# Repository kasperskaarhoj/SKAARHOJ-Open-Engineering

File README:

SKAARHOJ Open Engineering repository contains most of the freely available information on our hardware designs. You can find much more information about this project at http://skaarhoj.com/ and specifically the wiki pages at http://skaarhoj.com/wiki/

License:
All software is GNU-GPL and everything else is Creative Commons BY-SA unless otherwise noted. Please check out this page for information on how to use our free resources:

http://skaarhoj.com/about/licenses/

The SKAARHOJ Development Team

Kasper Skårhøj

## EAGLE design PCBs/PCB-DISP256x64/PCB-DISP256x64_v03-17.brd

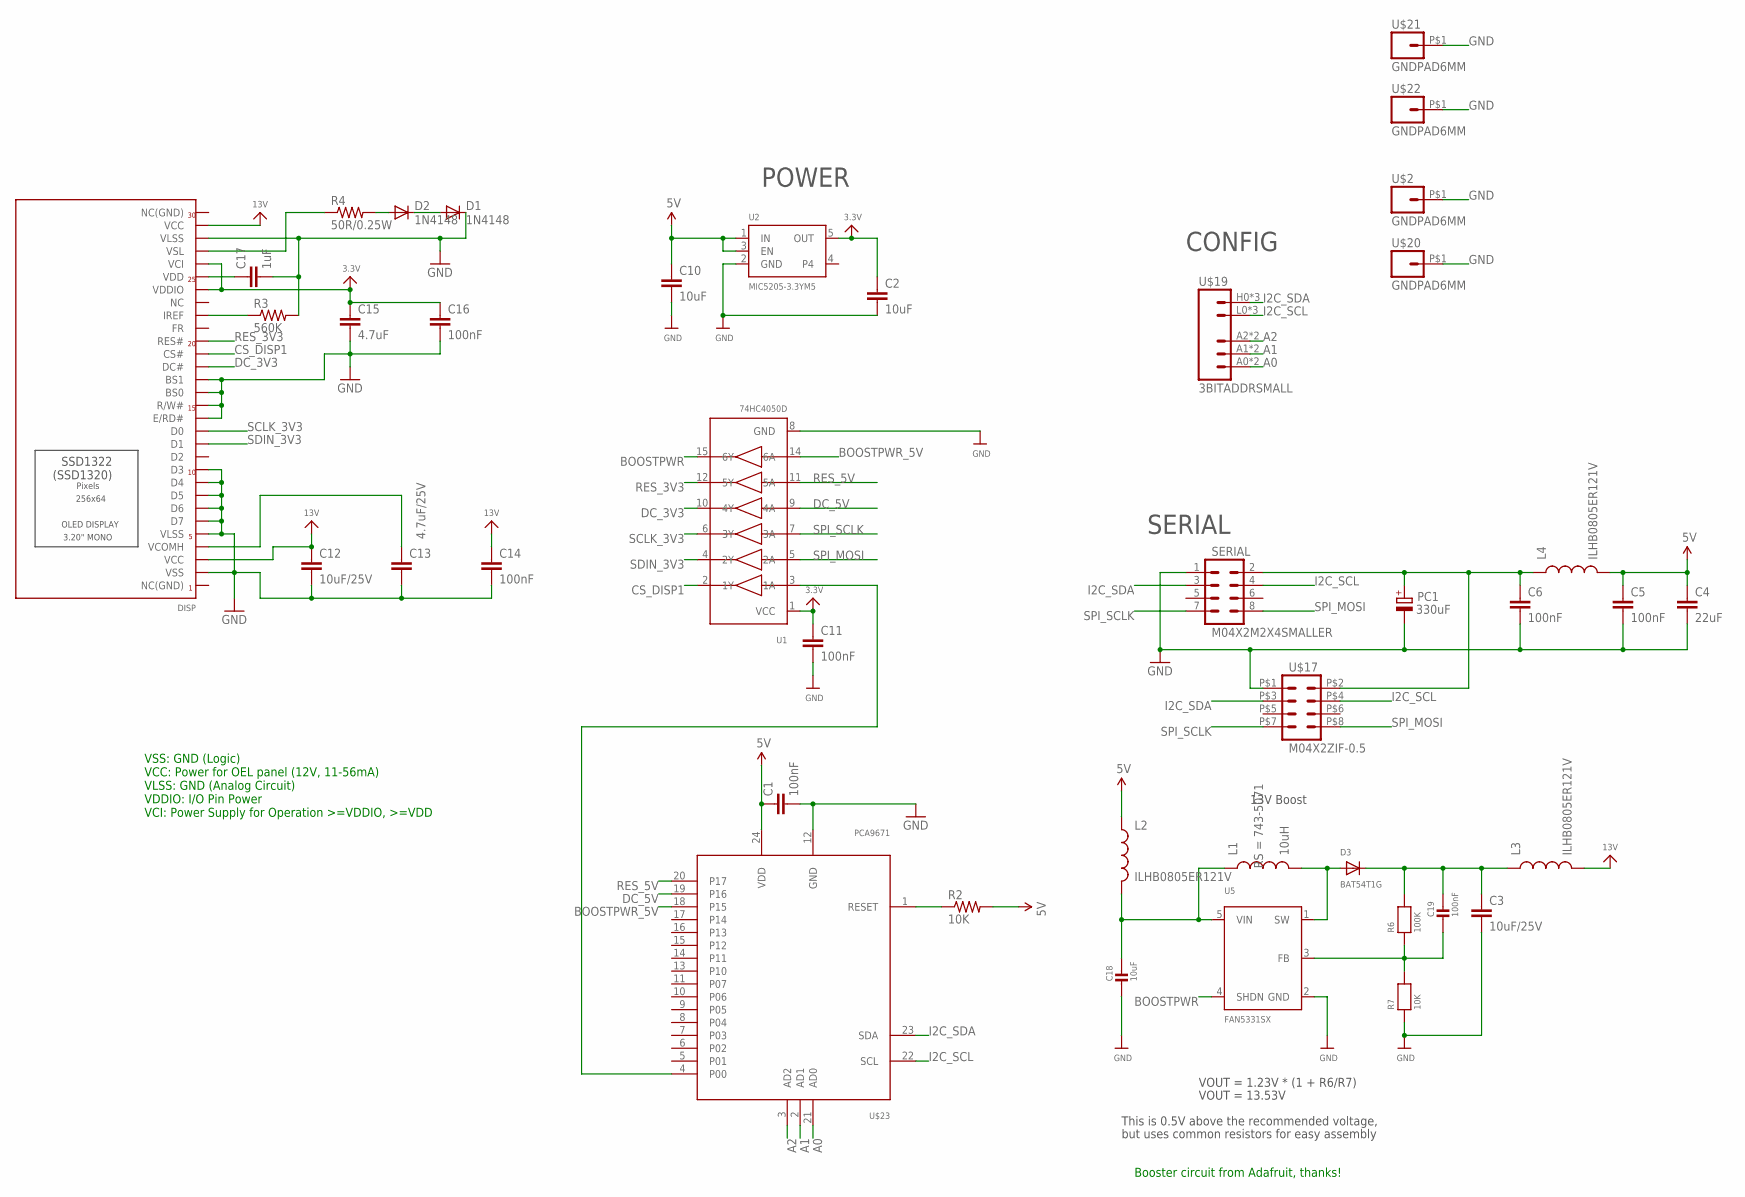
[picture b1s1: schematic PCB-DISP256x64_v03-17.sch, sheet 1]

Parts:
C1, C5, C6, C11, C14, C16: 100nF; 0603-CAP
C2, C10, C18: 10uF; 0805
C3, C12: 10uF/25V; 0805
C4: 22uF; 0805
C13: 4.7uF/25V; 0805
C15: 4.7uF; 0805
C17: 1uF; 0603-CAP
C19: 100nF; 0603
D1, D2: 1N4148; SOD-323
D3: BAT54T1G; SOD-123
DISP: ER_OLED032-1TOP; FPC_XF2M-3015-1A
L1: 10uH; 3015
L2, L3, L4: ILHB0805ER121V; 0805
PC1: 330uF; PANASONIC_D
R2: 10K; 0603-RES
R3: 560K; 0603-RES
R4: 50R/0.25W; 0603-RES
R6: 100K; 0603
R7: 10K; 0603
SERIAL: M04X2M2X4SMALLER; M2X4SMALLER
U1: 74HC4050D; TSSOP16
U2: MIC5205-3.3YM5; SOT23-5
U5: FAN5331SX; SOT23-5@1
U$2, U$20, U$21, U$22: GNDPAD6MM; 3.2MMPAD6MM
U$17: M04X2ZIF-0.5; ZIP-8-0.5
U$19: 3BITADDRSMALL; 3BITADDR_SMALL
U$23: PCA9671; TSSOP24

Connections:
3.3V: C2.1, C11.1, C15.1, C16.1, DISP.P$5 (VCI), DISP.P$7 (VDDIO), U1.1 (VCC), U2.5 (OUT)
5V: C1.1, C4.1, C5.1, C10.1, L2.1, L4.2, R2.2, U2.1 (IN), U2.3 (EN), U$23.24 (VDD)
13V: C12.1, C14.1, DISP.P$2 (VCC), DISP.P$28 (VCC), L3.2
A0: U$19.A0, U$19.AS0 (A0), U$23.21 (AD0)
A1: U$19.A1, U$19.AS1 (A1), U$23.2 (AD1)
A2: U$19.A2, U$19.AS2 (A2), U$23.3 (AD2)
ARD_5V: C6.1, L4.1, PC1.+, SERIAL.2, U$17.P$2 (2)
BOOSTPWR: U1.15 (6Y), U5.4 (SHDN)
BOOSTPWR_5V: U1.14 (6A), U$23.18 (P15)
CS_DISP1: DISP.P$12 (CS#), U1.2 (1Y)
DC_3V3: DISP.P$13 (DC#), U1.10 (4Y)
DC_5V: U1.9 (4A), U$23.19 (P16)
GND: C1.2, C2.2, C3.2, C4.2, C5.2, C6.2, C10.2, C11.2, C12.2, C13.2, C14.2, C15.2, C16.2, C17.2, C18.2, D1.1 (C), DISP.P$3 (VLSS), DISP.P$14 (BS1), DISP.P$15 (BS0), DISP.P$16 (R/W#), DISP.P$17 (E/RD#), DISP.P$21 (D3), DISP.P$22 (D4), DISP.P$23 (D5), DISP.P$24 (D6), DISP.P$25 (D7), DISP.P$26 (VLSS), DISP.P$29 (VSS), PC1.-, R3.2, R7.1, SERIAL.1, U1.8 (GND), U2.2 (GND), U5.2 (GND), U$2.P$1, U$17.P$1 (1), U$20.P$1, U$21.P$1, U$22.P$1, U$23.12 (GND)
I2C_SCL: SERIAL.4, U$17.P$4 (4), U$19.L0 (GND), U$19.L1 (GND), U$19.L2 (GND), U$23.22 (SCL)
I2C_SDA: SERIAL.3, U$17.P$3 (3), U$19.H0 (VCC), U$19.H1 (VCC), U$19.H2 (VCC), U$23.23 (SDA)
unnamed: R2.1, U$23.1 (RESET)
unnamed: C18.1, L1.1, L2.2, U5.5 (VIN)
unnamed: U1.3 (1A), U$23.4 (P00)
unnamed: C3.1, C19.1, D3.C, L3.1, R6.2
unnamed: C13.1, DISP.P$27 (VCOMH)
unnamed: DISP.P$4 (VSL), R4.1
unnamed: DISP.P$9 (IREF), R3.1
unnamed: D2.2 (A), R4.2
unnamed: C17.1, DISP.P$6 (VDD)
unnamed: D1.2 (A), D2.1 (C)
unnamed: D3.A, L1.2, U5.1 (SW)
unnamed: C19.2, R6.1, R7.2, U5.3 (FB)
RES_3V3: DISP.P$11 (RES#), U1.12 (5Y)
RES_5V: U1.11 (5A), U$23.20 (P17)
SCLK_3V3: DISP.P$18 (D0), U1.6 (3Y)
SDIN_3V3: DISP.P$19 (D1), U1.4 (2Y)
SPI_MOSI: SERIAL.8, U1.5 (2A), U$17.P$8 (8)
SPI_SCLK: SERIAL.7, U1.7 (3A), U$17.P$7 (7)

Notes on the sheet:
SERIAL
POWER
CONFIG
VOUT = 1.23V * (1 + R6/R7)
VOUT = 13.53V
This is 0.5V above the recommended voltage,
but uses common resistors for easy assembly
13V Boost
Booster circuit from Adafruit, thanks!
VSS: GND (Logic) VCC: Power for OEL panel (12V, 11-56mA) VLSS: GND (Analog Circuit) VDDIO: I/O Pin Power VCI: Power Supply for Operation >=VDDIO, >=VDD

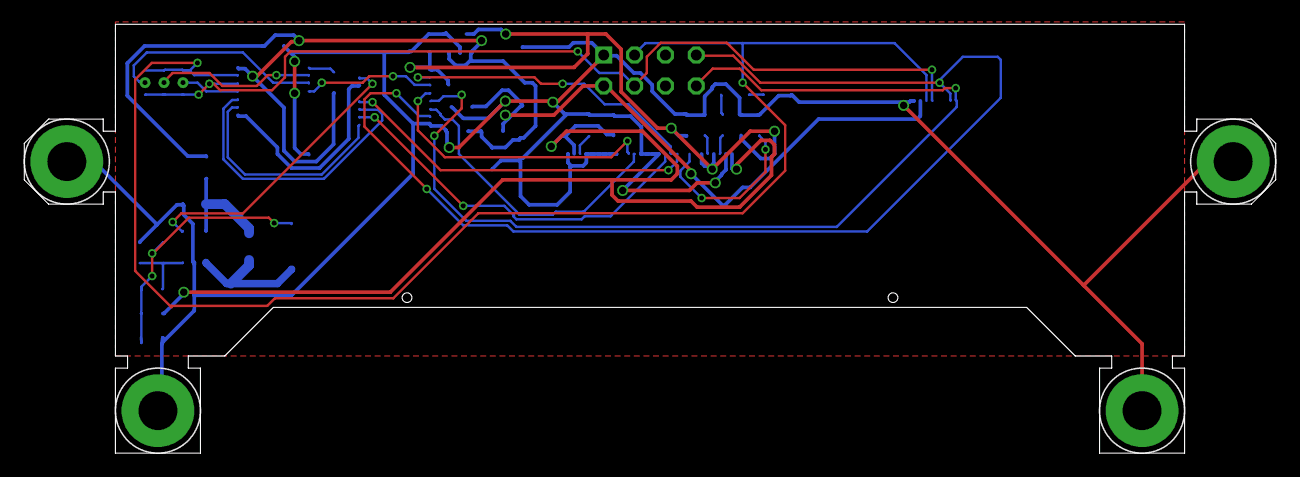
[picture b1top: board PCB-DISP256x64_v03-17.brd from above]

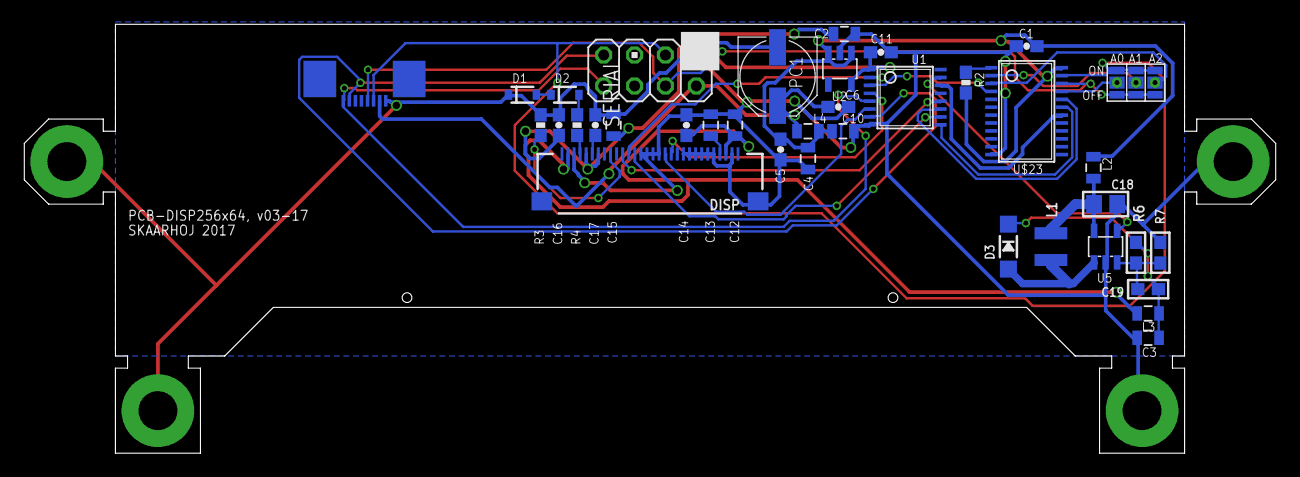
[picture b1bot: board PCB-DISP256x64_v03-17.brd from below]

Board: 2 copper layers, 103.0 x 35.3 mm, 41 parts (37 on the bottom side), 33 nets.

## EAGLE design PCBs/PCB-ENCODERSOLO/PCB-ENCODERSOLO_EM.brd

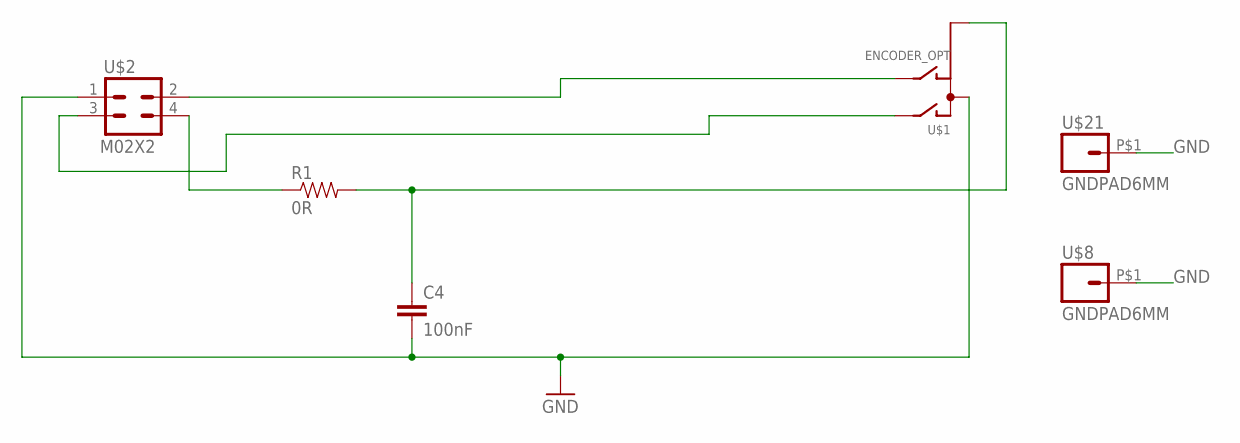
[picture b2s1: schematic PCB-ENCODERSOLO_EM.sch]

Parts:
C4: 100nF; 0603-CAP
R1: 0R; 0603-RES
U$1: ENCODER_OPT; ENCODER_EM14
U$2: M02X2; 2X2
U$8, U$21: GNDPAD6MM; 3.2MMPAD6MM

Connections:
5V: C4.1, R1.2, U$1.2 (5V)
D3: U$1.5 (A), U$2.3
GND: C4.2, U$1.6 (GND), U$1.GND, U$1.GND1 (GND), U$2.1, U$8.P$1, U$21.P$1
unnamed: R1.1, U$2.4
unnamed: U$1.1 (B), U$2.2

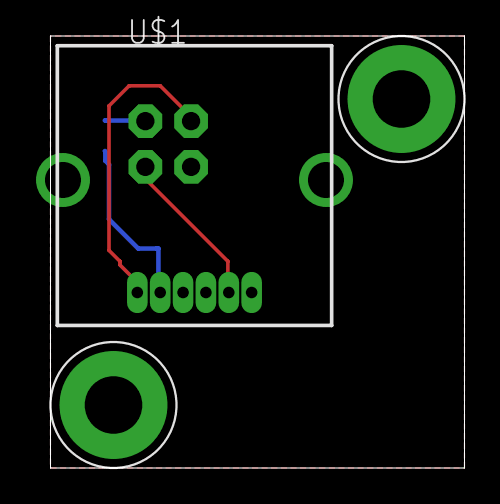
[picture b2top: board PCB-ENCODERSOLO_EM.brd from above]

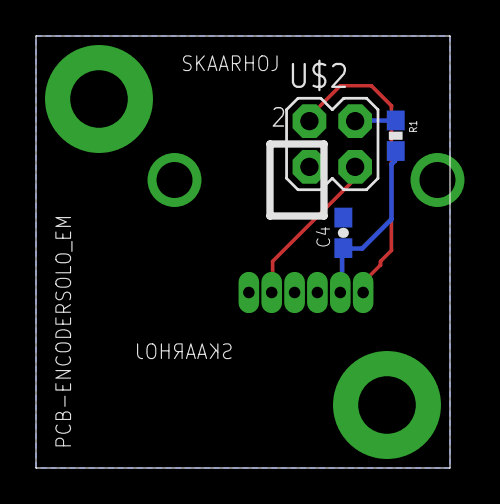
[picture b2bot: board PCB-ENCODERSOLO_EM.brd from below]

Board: 2 copper layers, 23.0 x 24.0 mm, 6 parts (3 on the bottom side), 5 nets.

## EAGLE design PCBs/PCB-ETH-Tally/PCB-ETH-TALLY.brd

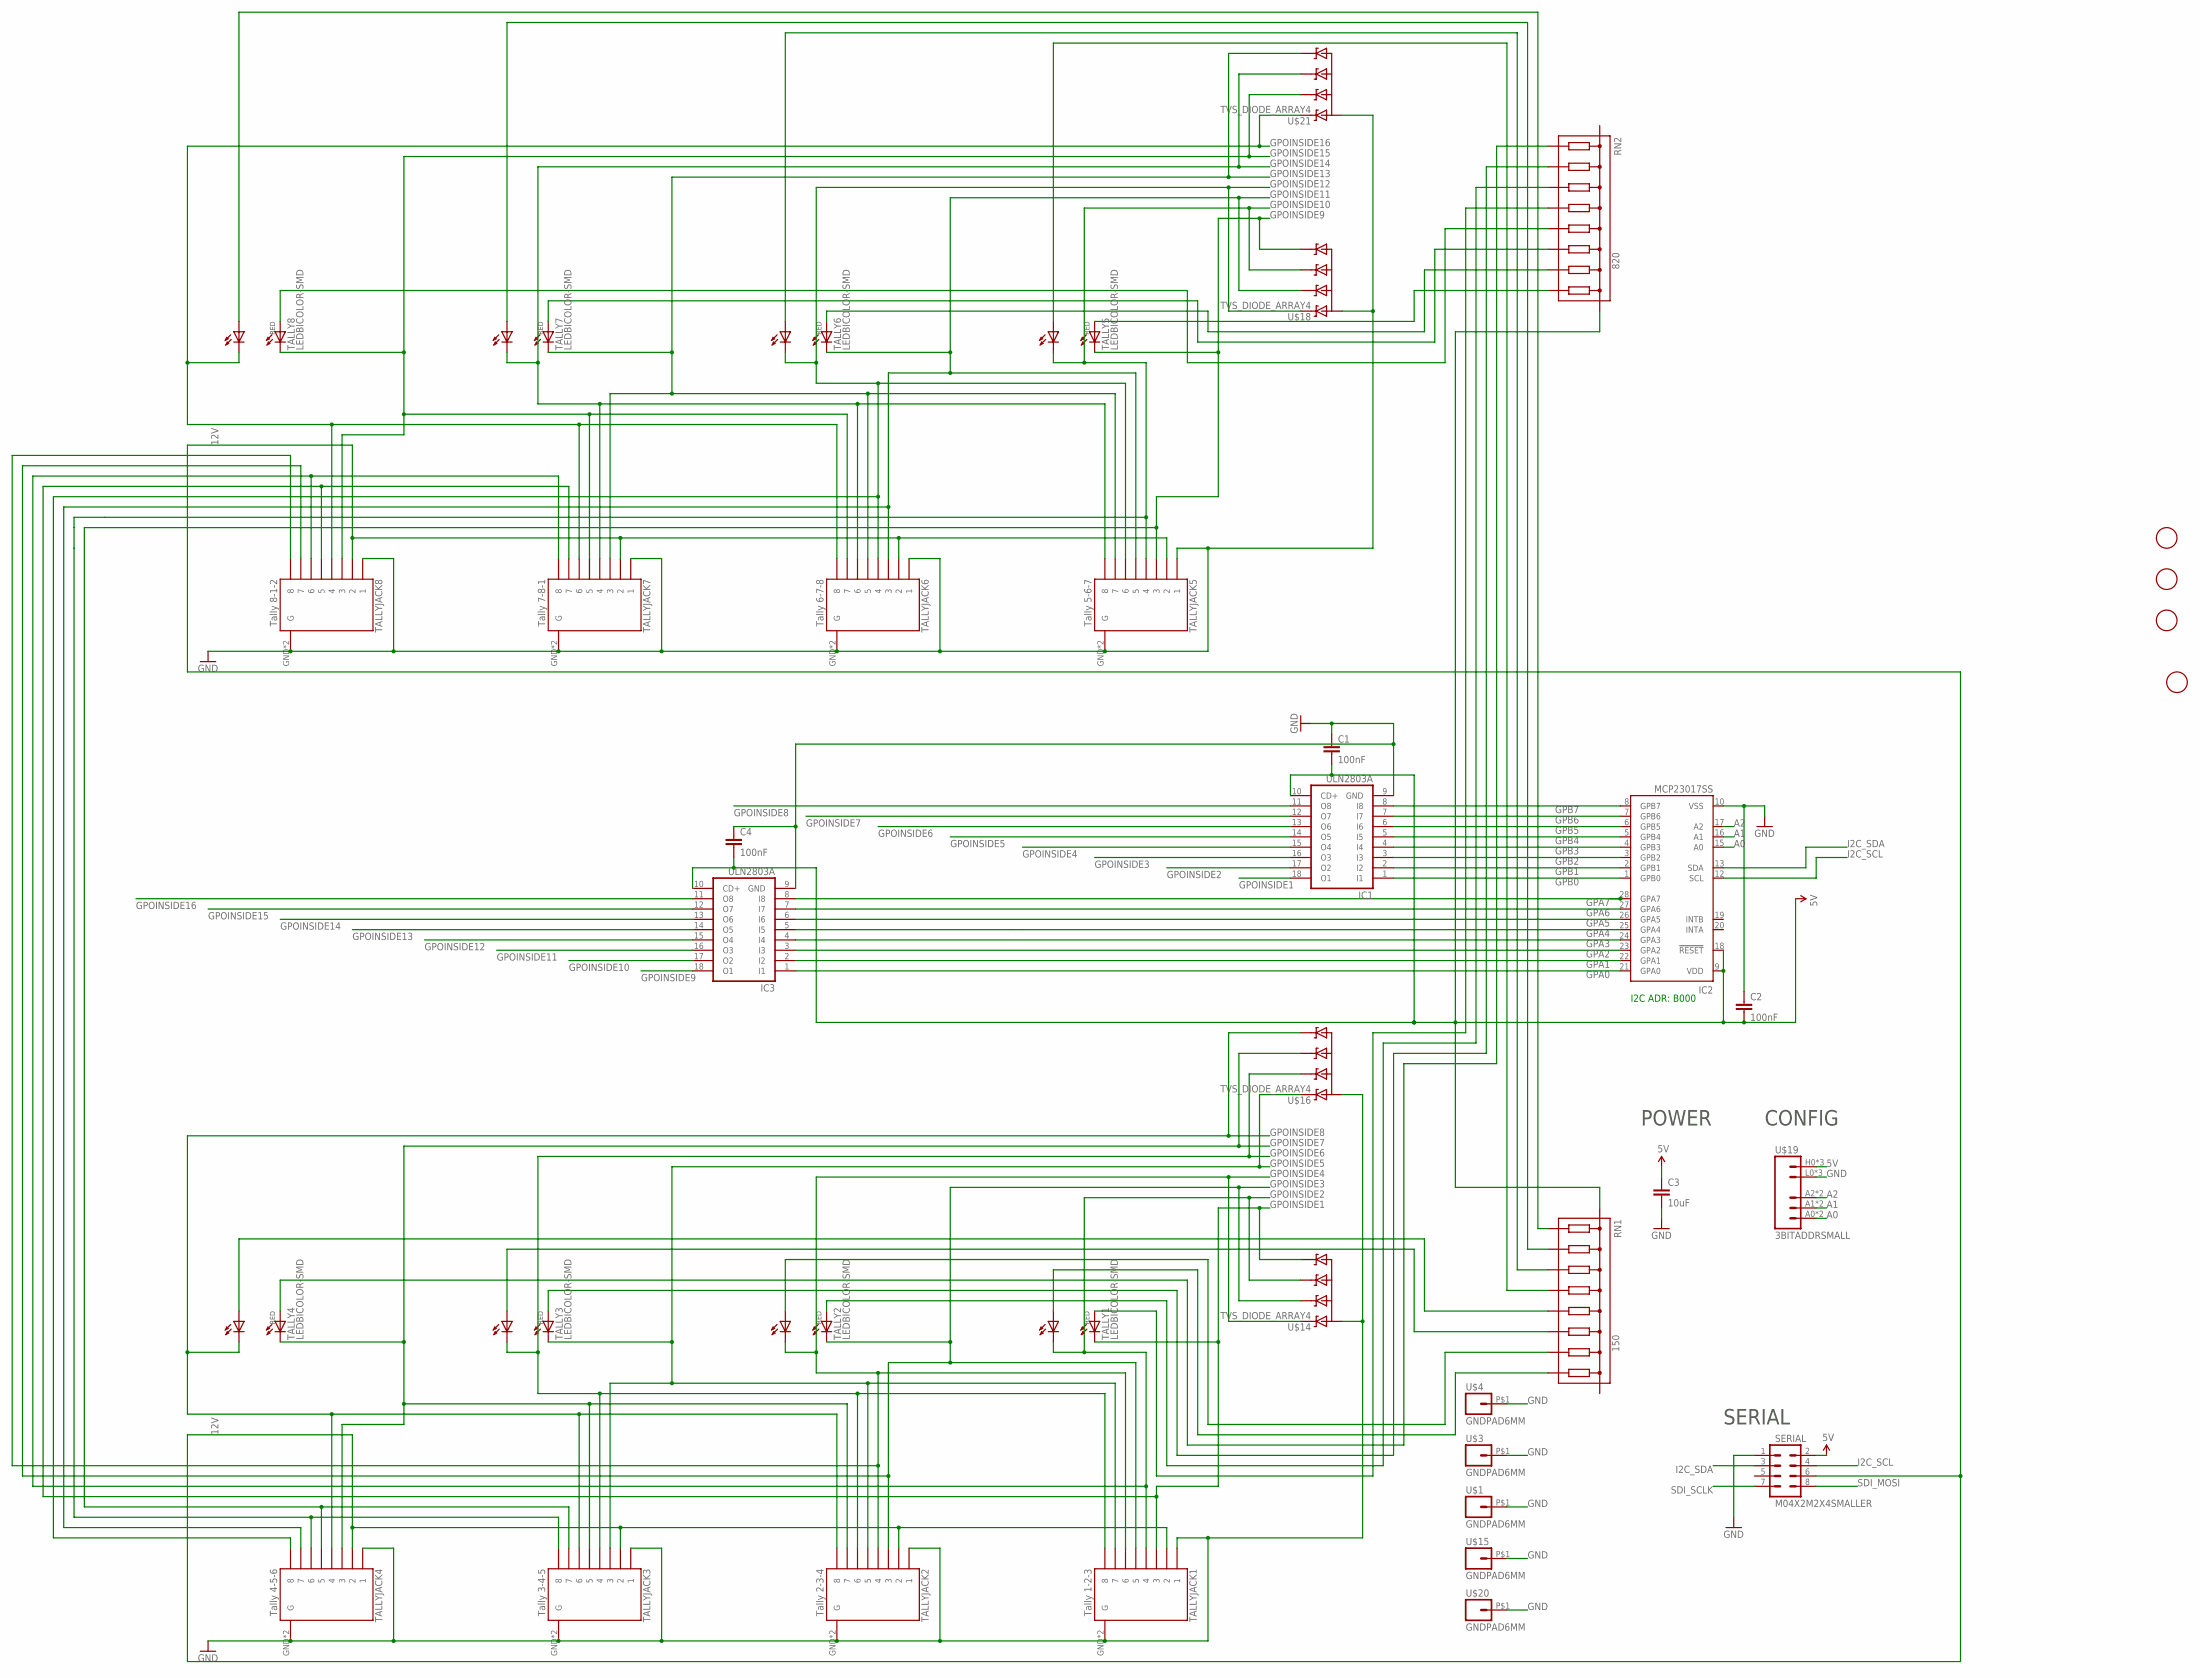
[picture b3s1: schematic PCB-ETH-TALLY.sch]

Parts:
C1, C4: 100nF; 0805
C2: 100nF; 0603-CAP
C3: 10uF; 0805
IC1, IC3: ULN2803A; SO18W
IC2: MCP23017SS; SSOP28
RN1: 150; EXBE
RN2: 820; EXBE
SERIAL: M04X2M2X4SMALLER; M2X4SMALLER
TALLY1, TALLY2, TALLY3, TALLY4, TALLY5, TALLY6, TALLY7, TALLY8: LEDBICOLOR-SMD
TALLYJACK1: Tally 1-2-3; RJ45-8_GND_UPRIGHT
TALLYJACK2: Tally 2-3-4; RJ45-8_GND_UPRIGHT
TALLYJACK3: Tally 3-4-5; RJ45-8_GND_UPRIGHT
TALLYJACK4: Tally 4-5-6; RJ45-8_GND_UPRIGHT
TALLYJACK5: Tally 5-6-7; RJ45-8_GND_UPRIGHT
TALLYJACK6: Tally 6-7-8; RJ45-8_GND_UPRIGHT
TALLYJACK7: Tally 7-8-1; RJ45-8_GND_UPRIGHT
TALLYJACK8: Tally 8-1-2; RJ45-8_GND_UPRIGHT
U$1, U$3, U$4, U$15, U$20: GNDPAD6MM; 3.2MMPAD6MM
U$5, U$6, U$8, U$9: FIDUCIAL; FIDUCIAL_1MM
U$14, U$16, U$18, U$21: TVS_DIODE_ARRAY4; SOT23-6L
U$19: 3BITADDRSMALL; 3BITADDR_SMALL

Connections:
5V: C1.2, C2.2, C3.1, C4.2, IC1.10 (CD+), IC2.9 (VDD), IC2.18 (!RESET), IC3.10 (CD+), RN1.1 (POL), RN2.6 (POL), SERIAL.2, U$19.H0 (VCC), U$19.H1 (VCC), U$19.H2 (VCC)
12V: SERIAL.6, TALLYJACK1.2, TALLYJACK2.2, TALLYJACK3.2, TALLYJACK4.2, TALLYJACK5.2, TALLYJACK6.2, TALLYJACK7.2, TALLYJACK8.2
A0: IC2.15 (A0), U$19.A0, U$19.AS0 (A0)
A1: IC2.16 (A1), U$19.A1, U$19.AS1 (A1)
A2: IC2.17 (A2), U$19.A2, U$19.AS2 (A2)
GND: C1.1, C2.1, C3.2, C4.1, IC1.9 (GND), IC2.10 (VSS), IC3.9 (GND), SERIAL.1, TALLYJACK1.1, TALLYJACK1.GND (G), TALLYJACK1.GND1 (G), TALLYJACK2.1, TALLYJACK2.GND (G), TALLYJACK2.GND1 (G), TALLYJACK3.1, TALLYJACK3.GND (G), TALLYJACK3.GND1 (G), TALLYJACK4.1, TALLYJACK4.GND (G), TALLYJACK4.GND1 (G), TALLYJACK5.1, TALLYJACK5.GND (G), TALLYJACK5.GND1 (G), TALLYJACK6.1, TALLYJACK6.GND (G), TALLYJACK6.GND1 (G), TALLYJACK7.1, TALLYJACK7.GND (G), TALLYJACK7.GND1 (G), TALLYJACK8.1, TALLYJACK8.GND (G), TALLYJACK8.GND1 (G), U$1.P$1, U$3.P$1, U$4.P$1, U$14.2 (GND), U$14.5 (GND), U$15.P$1, U$16.2 (GND), U$16.5 (GND), U$18.2 (GND), U$18.5 (GND), U$19.L0 (GND), U$19.L1 (GND), U$19.L2 (GND), U$20.P$1, U$21.2 (GND), U$21.5 (GND)
GPA0: IC2.21 (GPA0), IC3.1 (I1)
GPA1: IC2.22 (GPA1), IC3.2 (I2)
GPA2: IC2.23 (GPA2), IC3.3 (I3)
GPA3: IC2.24 (GPA3), IC3.4 (I4)
GPA4: IC2.25 (GPA4), IC3.5 (I5)
GPA5: IC2.26 (GPA5), IC3.6 (I6)
GPA6: IC2.27 (GPA6), IC3.7 (I7)
GPA7: IC2.28 (GPA7), IC3.8 (I8)
GPB0: IC1.1 (I1), IC2.1 (GPB0)
GPB1: IC1.2 (I2), IC2.2 (GPB1)
GPB2: IC1.3 (I3), IC2.3 (GPB2)
GPB3: IC1.4 (I4), IC2.4 (GPB3)
GPB4: IC1.5 (I5), IC2.5 (GPB4)
GPB5: IC1.6 (I6), IC2.6 (GPB5)
GPB6: IC1.7 (I7), IC2.7 (GPB6)
GPB7: IC1.8 (I8), IC2.8 (GPB7)
GPOINSIDE1: IC1.18 (O1), TALLY1.P$2 (C), TALLYJACK1.3, TALLYJACK7.7, TALLYJACK8.5, U$14.6 (D)
GPOINSIDE2: IC1.17 (O2), TALLY1.P$4 (C1), TALLYJACK1.4, TALLYJACK7.8, TALLYJACK8.6, U$14.4 (C)
GPOINSIDE3: IC1.16 (O3), TALLY2.P$2 (C), TALLYJACK1.5, TALLYJACK2.3, TALLYJACK8.7, U$14.3 (B)
GPOINSIDE4: IC1.15 (O4), TALLY2.P$4 (C1), TALLYJACK1.6, TALLYJACK2.4, TALLYJACK8.8, U$14.1 (A)
GPOINSIDE5: IC1.14 (O5), TALLY3.P$2 (C), TALLYJACK1.7, TALLYJACK2.5, TALLYJACK3.3, U$16.1 (A)
GPOINSIDE6: IC1.13 (O6), TALLY3.P$4 (C1), TALLYJACK1.8, TALLYJACK2.6, TALLYJACK3.4, U$16.3 (B)
GPOINSIDE7: IC1.12 (O7), TALLY4.P$2 (C), TALLYJACK2.7, TALLYJACK3.5, TALLYJACK4.3, U$16.4 (C)
GPOINSIDE8: IC1.11 (O8), TALLY4.P$4 (C1), TALLYJACK2.8, TALLYJACK3.6, TALLYJACK4.4, U$16.6 (D)
GPOINSIDE9: IC3.18 (O1), TALLY5.P$2 (C), TALLYJACK3.7, TALLYJACK4.5, TALLYJACK5.3, U$18.6 (D)
GPOINSIDE10: IC3.17 (O2), TALLY5.P$4 (C1), TALLYJACK3.8, TALLYJACK4.6, TALLYJACK5.4, U$18.4 (C)
GPOINSIDE11: IC3.16 (O3), TALLY6.P$2 (C), TALLYJACK4.7, TALLYJACK5.5, TALLYJACK6.3, U$18.3 (B)
GPOINSIDE12: IC3.15 (O4), TALLY6.P$4 (C1), TALLYJACK4.8, TALLYJACK5.6, TALLYJACK6.4, U$18.1 (A)
GPOINSIDE13: IC3.14 (O5), TALLY7.P$2 (C), TALLYJACK5.7, TALLYJACK6.5, TALLYJACK7.3, U$21.6 (D)
GPOINSIDE14: IC3.13 (O6), TALLY7.P$4 (C1), TALLYJACK5.8, TALLYJACK6.6, TALLYJACK7.4, U$21.4 (C)
GPOINSIDE15: IC3.12 (O7), TALLY8.P$2 (C), TALLYJACK6.7, TALLYJACK7.5, TALLYJACK8.3, U$21.3 (B)
GPOINSIDE16: IC3.11 (O8), TALLY8.P$4 (C1), TALLYJACK6.8, TALLYJACK7.6, TALLYJACK8.4, U$21.1 (A)
I2C_SCL: IC2.12 (SCL), SERIAL.4
I2C_SDA: IC2.13 (SDA), SERIAL.3
unnamed: RN2.10 (8), TALLY5.P$1 (A)
unnamed: RN2.9 (7), TALLY6.P$1 (A)
unnamed: RN2.8 (6), TALLY7.P$1 (A)
unnamed: RN2.7 (5), TALLY8.P$1 (A)
unnamed: RN2.5 (4), TALLY1.P$1 (A)
unnamed: RN2.4 (3), TALLY2.P$1 (A)
unnamed: RN2.2 (1), TALLY4.P$1 (A)
unnamed: RN2.3 (2), TALLY3.P$1 (A)
unnamed: RN1.10 (8), TALLY1.P$3 (A1)
unnamed: RN1.9 (7), TALLY2.P$3 (A1)
unnamed: RN1.8 (6), TALLY3.P$3 (A1)
unnamed: RN1.7 (5), TALLY4.P$3 (A1)
unnamed: RN1.5 (4), TALLY5.P$3 (A1)
unnamed: RN1.4 (3), TALLY6.P$3 (A1)
unnamed: RN1.3 (2), TALLY7.P$3 (A1)
unnamed: RN1.2 (1), TALLY8.P$3 (A1)
SDI_MOSI: SERIAL.8
SDI_SCLK: SERIAL.7

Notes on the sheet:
I2C ADR: B000
SERIAL
POWER
CONFIG

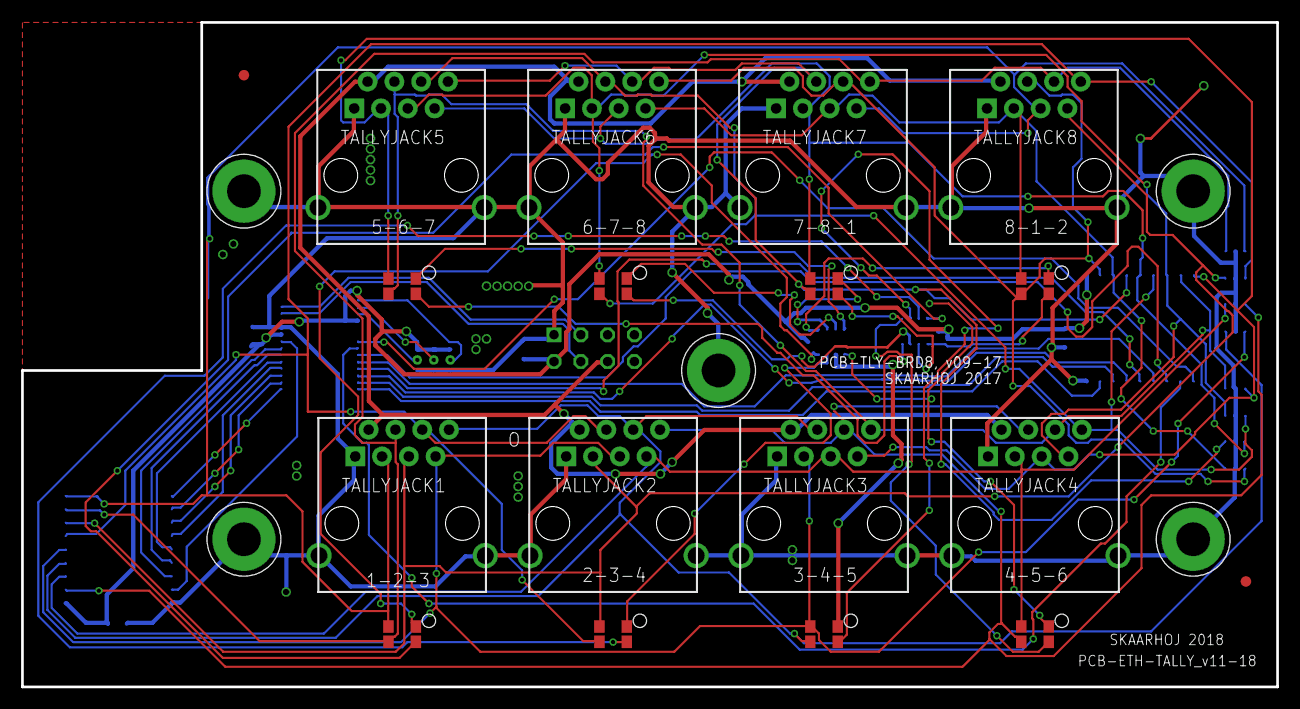
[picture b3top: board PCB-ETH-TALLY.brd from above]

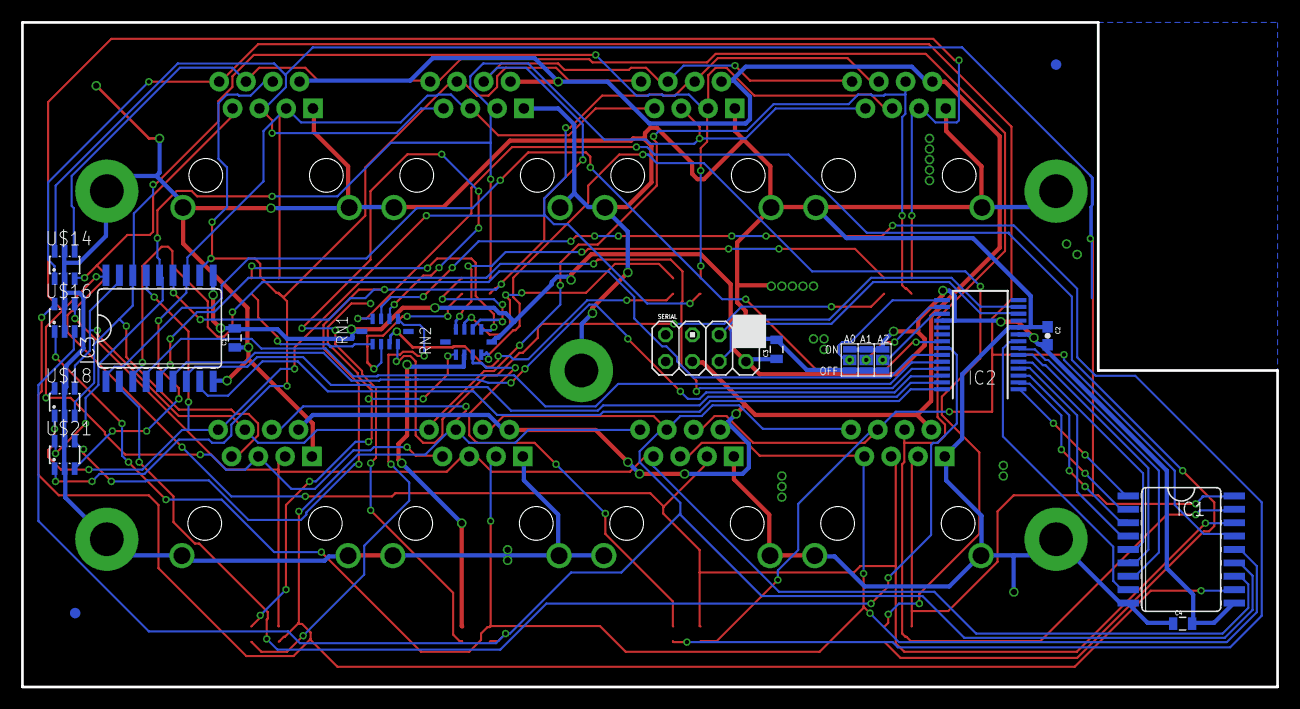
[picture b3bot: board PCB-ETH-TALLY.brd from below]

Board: 2 copper layers, 119.0 x 63.0 mm, 40 parts (17 on the bottom side), 56 nets.

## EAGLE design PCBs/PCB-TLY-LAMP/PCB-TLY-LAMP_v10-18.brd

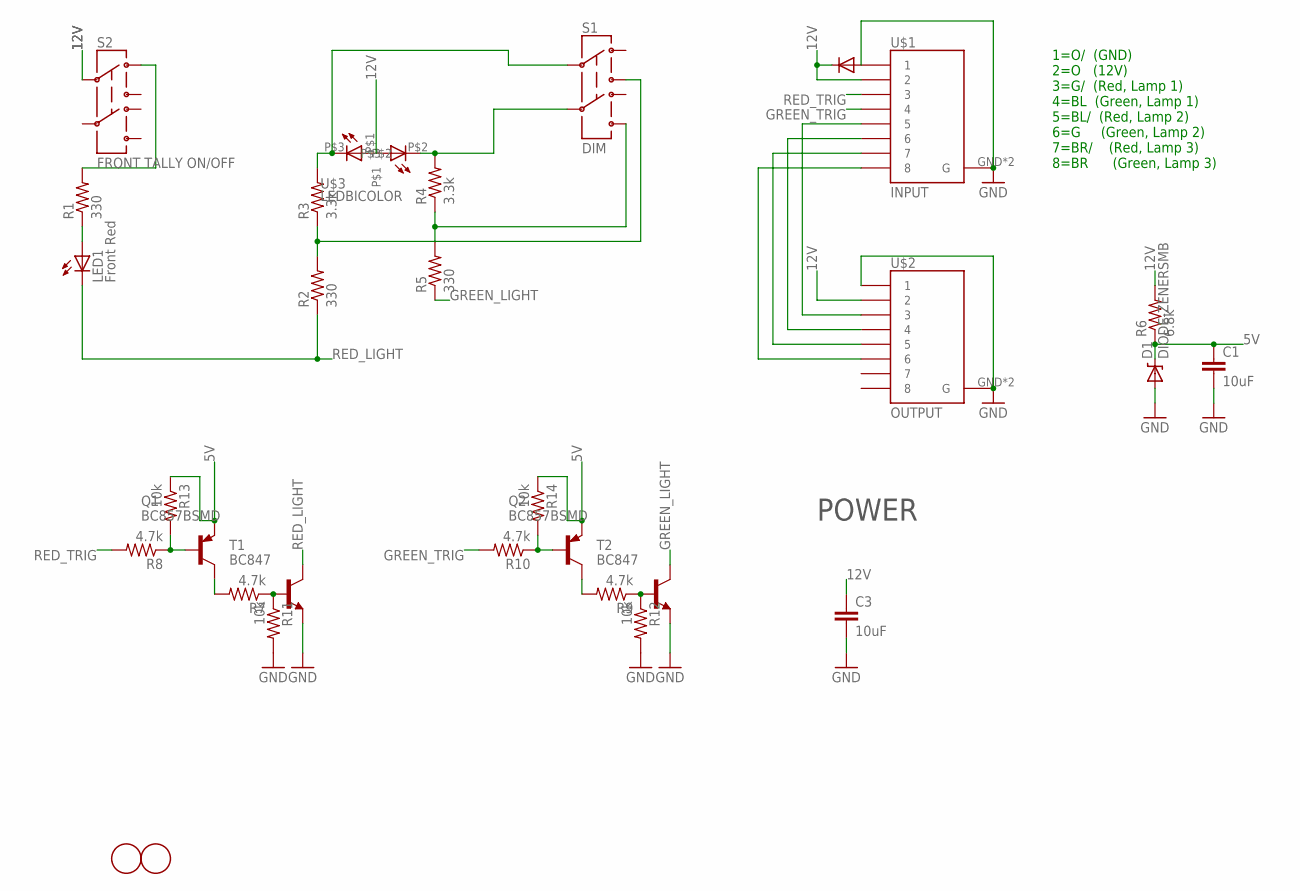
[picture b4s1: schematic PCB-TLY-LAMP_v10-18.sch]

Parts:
C1, C3: 10uF; 0805
D1: DIODE-ZENERSMB; SMB-DIODE
LED1: Front Red; LED20
Q1, Q2: BC857BSMD; SOT23-BEC
R1, R2, R5: 330; 0603-RES
R3, R4: 3.3k; 0603-RES
R6: 6.8k; 0603-RES
R7, R8, R9, R10: 4.7k; 0603-RES
R11, R12, R13, R14: 10k; 0603-RES
S1: DIM; TECONNECTIVITY-DPDT
S2: FRONT TALLY ON/OFF; TECONNECTIVITY-DPDT
T1, T2: BC847; SOT23
U$1: INPUT; RJ45-8_GND
U$2: OUTPUT; RJ45-8_GND
U$3: LEDBICOLOR
U$4, U$5: FIDUCIAL; FIDUCIAL_1MM

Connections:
5V: C1.1, D1.C, Q1.E, Q2.E, R6.1, R13.1, R14.1
12V: C3.1, R6.2, S2.P$2 (2), U$1.2, U$2.2, U$3.P$1
GND: C1.2, C3.2, D1.A, R11.2, R12.2, T1.2 (E), T2.2 (E), U$1.1, U$1.GND (G), U$1.GND1 (G), U$2.1, U$2.GND (G), U$2.GND1 (G)
GREEN_LIGHT: R5.1, T2.3 (C)
GREEN_TRIG: R10.2, U$1.4
unnamed: R1.2, S2.P$1 (1)
unnamed: LED1.P$1 (A), R1.1
unnamed: R2.2, R3.1, S1.P$3 (3)
unnamed: R4.1, R5.2, S1.P$6 (6)
unnamed: R4.2, S1.P$5 (5), U$3.P$2
unnamed: R3.2, S1.P$2 (2), U$3.P$3
unnamed: U$1.5, U$2.3
unnamed: U$1.6, U$2.4
unnamed: R7.1, R11.1, T1.1 (B)
unnamed: Q1.C, R7.2
unnamed: U$1.7, U$2.5
unnamed: U$1.8, U$2.6
unnamed: R9.1, R12.1, T2.1 (B)
unnamed: Q2.C, R9.2
unnamed: Q2.B, R10.1, R14.2
unnamed: Q1.B, R8.1, R13.2
RED_LIGHT: LED1.P$2 (C), R2.1, T1.3 (C)
RED_TRIG: R8.2, U$1.3

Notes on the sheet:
POWER
1=O/ (GND) 2=O (12V) 3=G/ (Red, Lamp 1) 4=BL (Green, Lamp 1) 5=BL/ (Red, Lamp 2) 6=G (Green, Lamp 2) 7=BR/ (Red, Lamp 3) 8=BR (Green, Lamp 3)

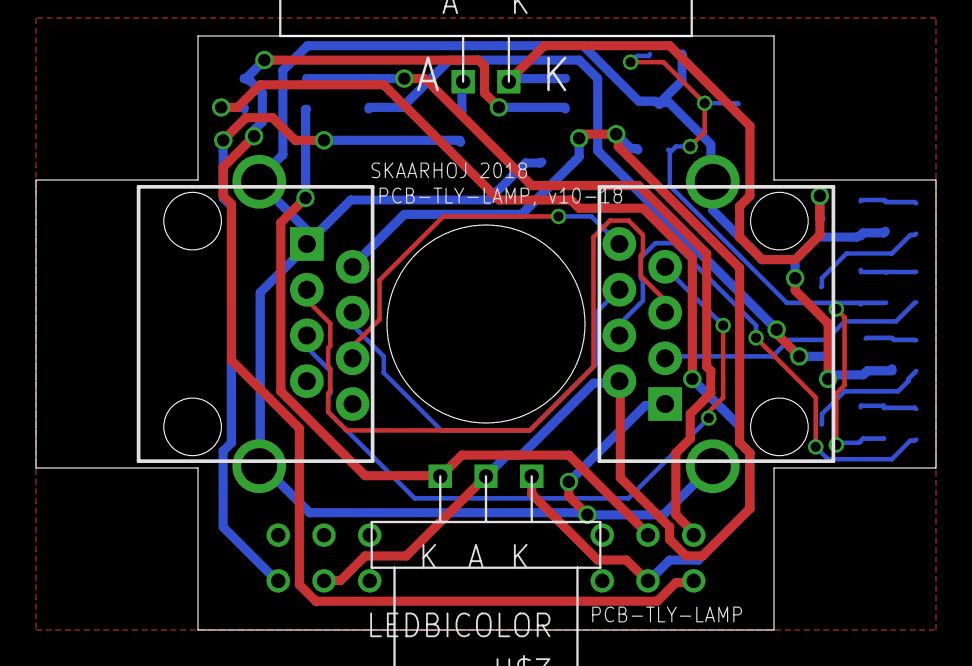
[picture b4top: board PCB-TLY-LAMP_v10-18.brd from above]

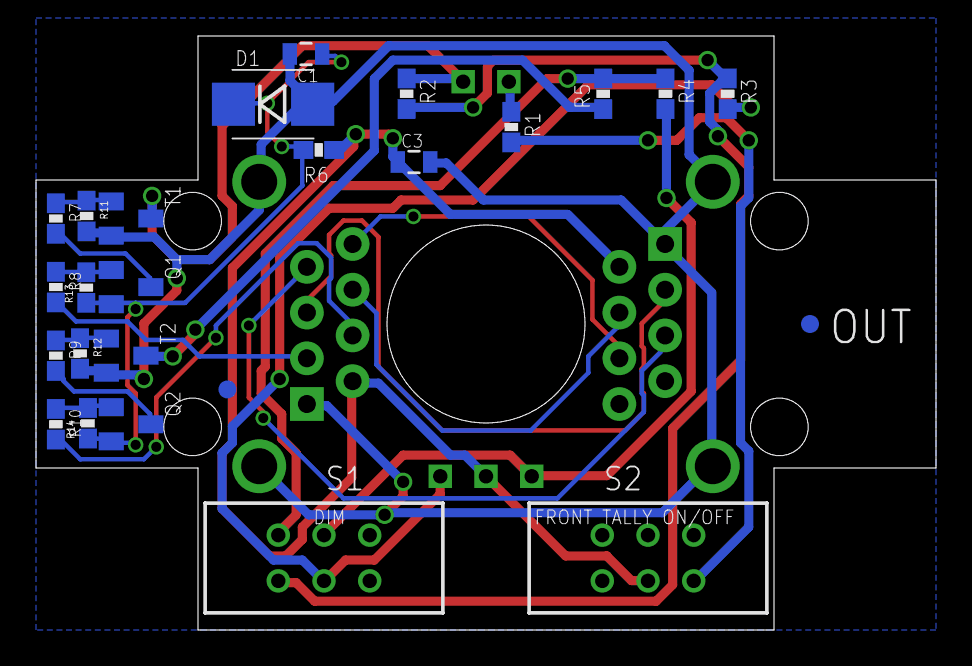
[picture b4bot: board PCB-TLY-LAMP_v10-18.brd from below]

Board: 2 copper layers, 50.0 x 33.0 mm, 29 parts (25 on the bottom side), 23 nets.

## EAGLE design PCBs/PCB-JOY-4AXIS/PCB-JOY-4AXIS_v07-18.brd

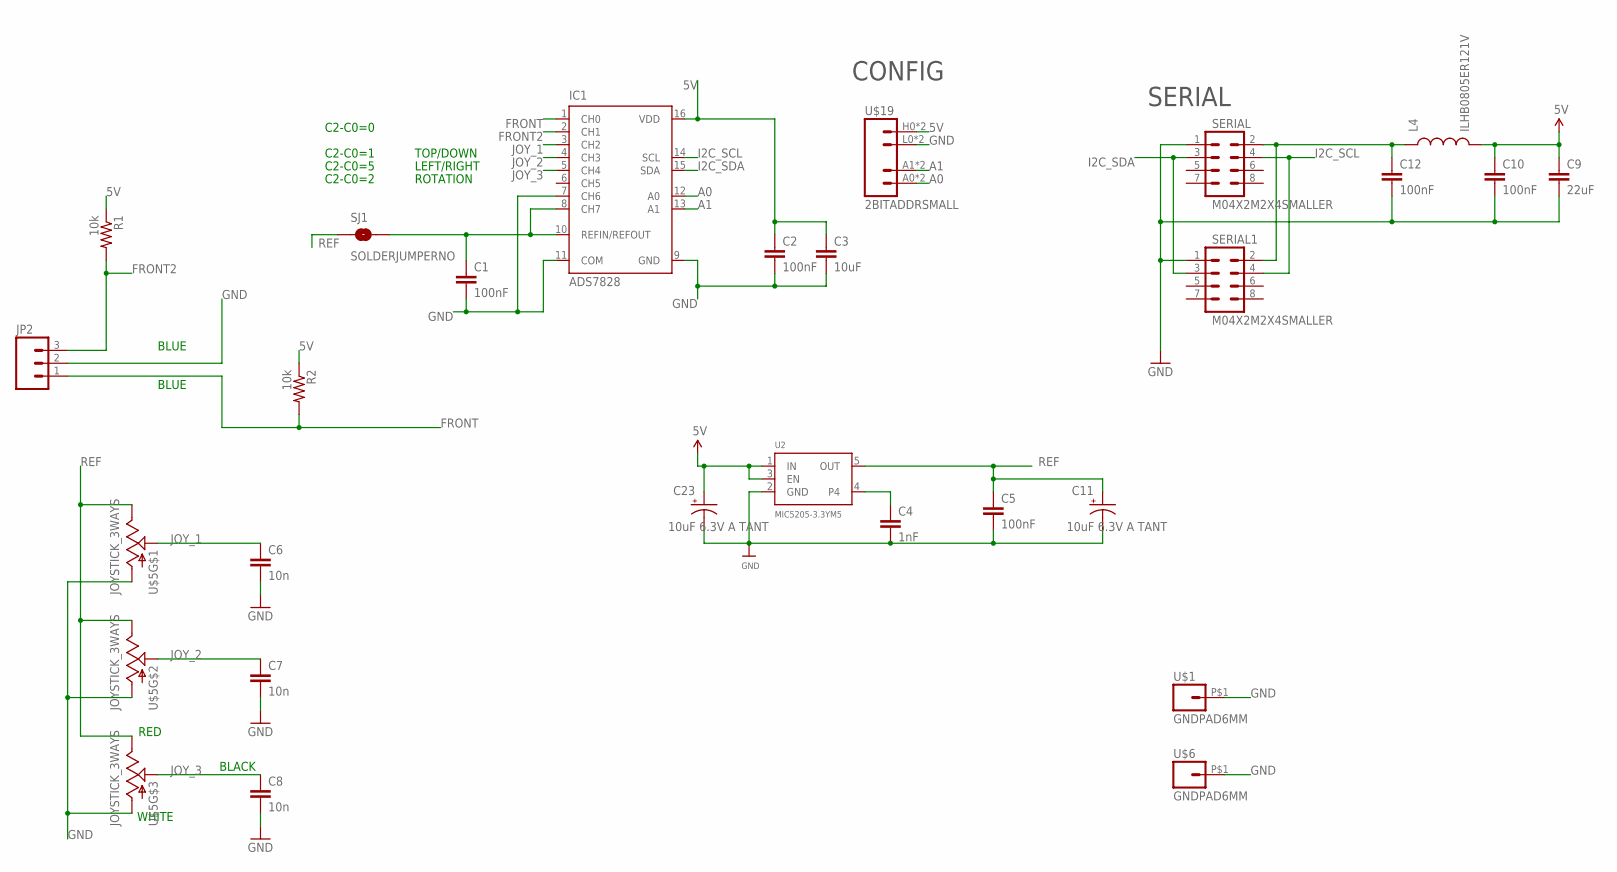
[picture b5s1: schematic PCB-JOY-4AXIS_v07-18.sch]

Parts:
C1, C2, C5, C10, C12: 100nF; 0603-CAP
C3: 10uF; 0805
C4: 1nF; 0603-CAP
C6, C7, C8: 10n; 0603-CAP
C9: 22uF; 0805
C11, C23: 10uF 6.3V A TANT; EIA3216
IC1: ADS7828; TSSOP16-PW
JP2: M03PTH; 1X03
L4: ILHB0805ER121V; 0805
R1, R2: 10k; 0603-RES
SERIAL, SERIAL1: M04X2M2X4SMALLER; M2X4SMALLER
SJ1: SOLDERJUMPERNO; SJ_2S-NO
U2: MIC5205-3.3YM5; SOT23-5
U$1, U$6: GNDPAD6MM; 3.2MMPAD6MM
U$5: JOYSTICK_3WAYS; JOYSTICK
U$19: 2BITADDRSMALL; 2BITADDR_SMALL

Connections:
5V: C2.1, C3.1, C9.1, C10.1, C23.A (+), IC1.16 (VDD), L4.2, R1.1, R2.1, U2.1 (IN), U2.3 (EN), U$19.H0 (VCC), U$19.H1 (VCC)
5V_AD: C1.1, IC1.8 (CH7), IC1.10 (REFIN/REFOUT), SJ1.2
A0: IC1.12 (A0), U$19.A0 (A1), U$19.AS0 (A1)
A1: IC1.13 (A1), U$19.A1 (A2), U$19.AS1 (A2)
ARD_5V: C12.1, L4.1, SERIAL.2, SERIAL1.2
FRONT: IC1.1 (CH0), JP2.1, R2.2
FRONT2: IC1.2 (CH1), JP2.3, R1.2
GND: C1.2, C2.2, C3.2, C4.2, C5.2, C6.2, C7.2, C8.2, C9.2, C10.2, C11.C (-), C12.2, C23.C (-), IC1.7 (CH6), IC1.9 (GND), IC1.11 (COM), JP2.2, SERIAL.1, SERIAL1.1, U2.2 (GND), U$1.P$1, U$5.LR_COM (A), U$5.ROT_COM (A), U$5.UD_COM (A), U$6.P$1, U$19.L0 (GND), U$19.L1 (GND)
I2C_SCL: IC1.14 (SCL), SERIAL.4, SERIAL1.4
I2C_SDA: IC1.15 (SDA), SERIAL.3, SERIAL1.3
JOY_1: C6.1, IC1.3 (CH2), U$5.LR_C (S)
JOY_2: C7.1, IC1.4 (CH3), U$5.UD_C (S)
JOY_3: C8.1, IC1.5 (CH4), U$5.ROT_C (S)
unnamed: C4.1, U2.4
REF: C5.1, C11.A (+), SJ1.1, U2.5 (OUT), U$5.LR_V (E), U$5.ROT_V (E), U$5.UD_V (E)

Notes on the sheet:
CONFIG
TOP/DOWN
LEFT/RIGHT
ROTATION
C2-C0=0
C2-C0=1
C2-C0=5
C2-C0=2
SERIAL
BLACK
RED
WHITE
BLUE

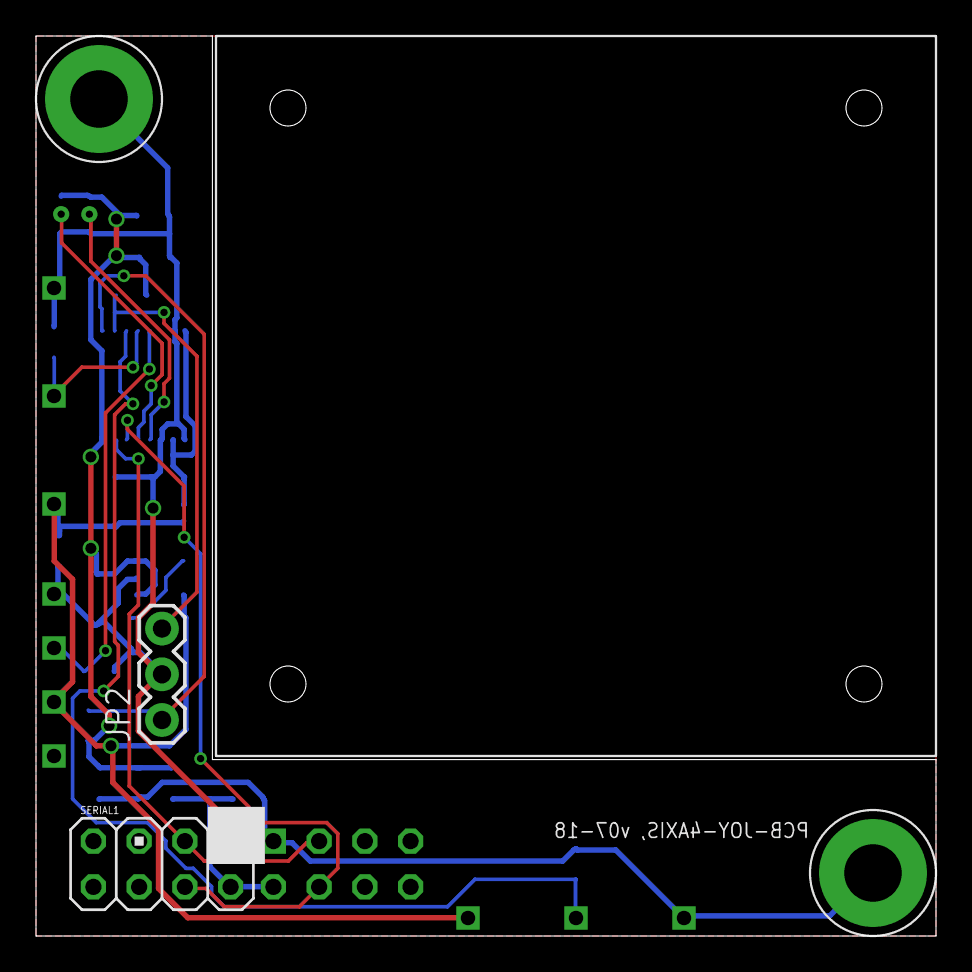
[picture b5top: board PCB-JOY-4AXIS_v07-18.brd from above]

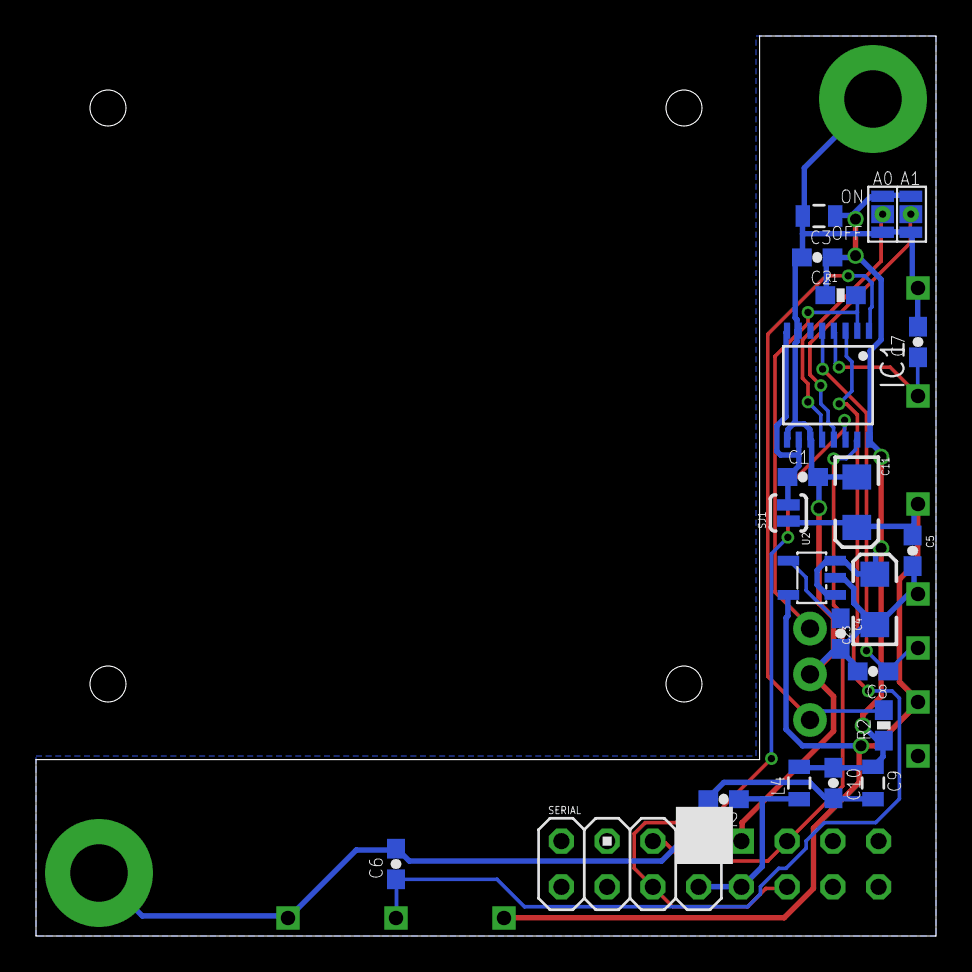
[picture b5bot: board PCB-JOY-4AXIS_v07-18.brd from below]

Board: 2 copper layers, 50.0 x 50.0 mm, 26 parts (21 on the bottom side), 15 nets.

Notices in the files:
parts and their libraries:
SparkFun: Licensing: CC v3.0 Share-Alike You are welcome to use this library for commercial purposes.
m-pad-2.1: License : GNU General Public License version 2 (see bottom)
